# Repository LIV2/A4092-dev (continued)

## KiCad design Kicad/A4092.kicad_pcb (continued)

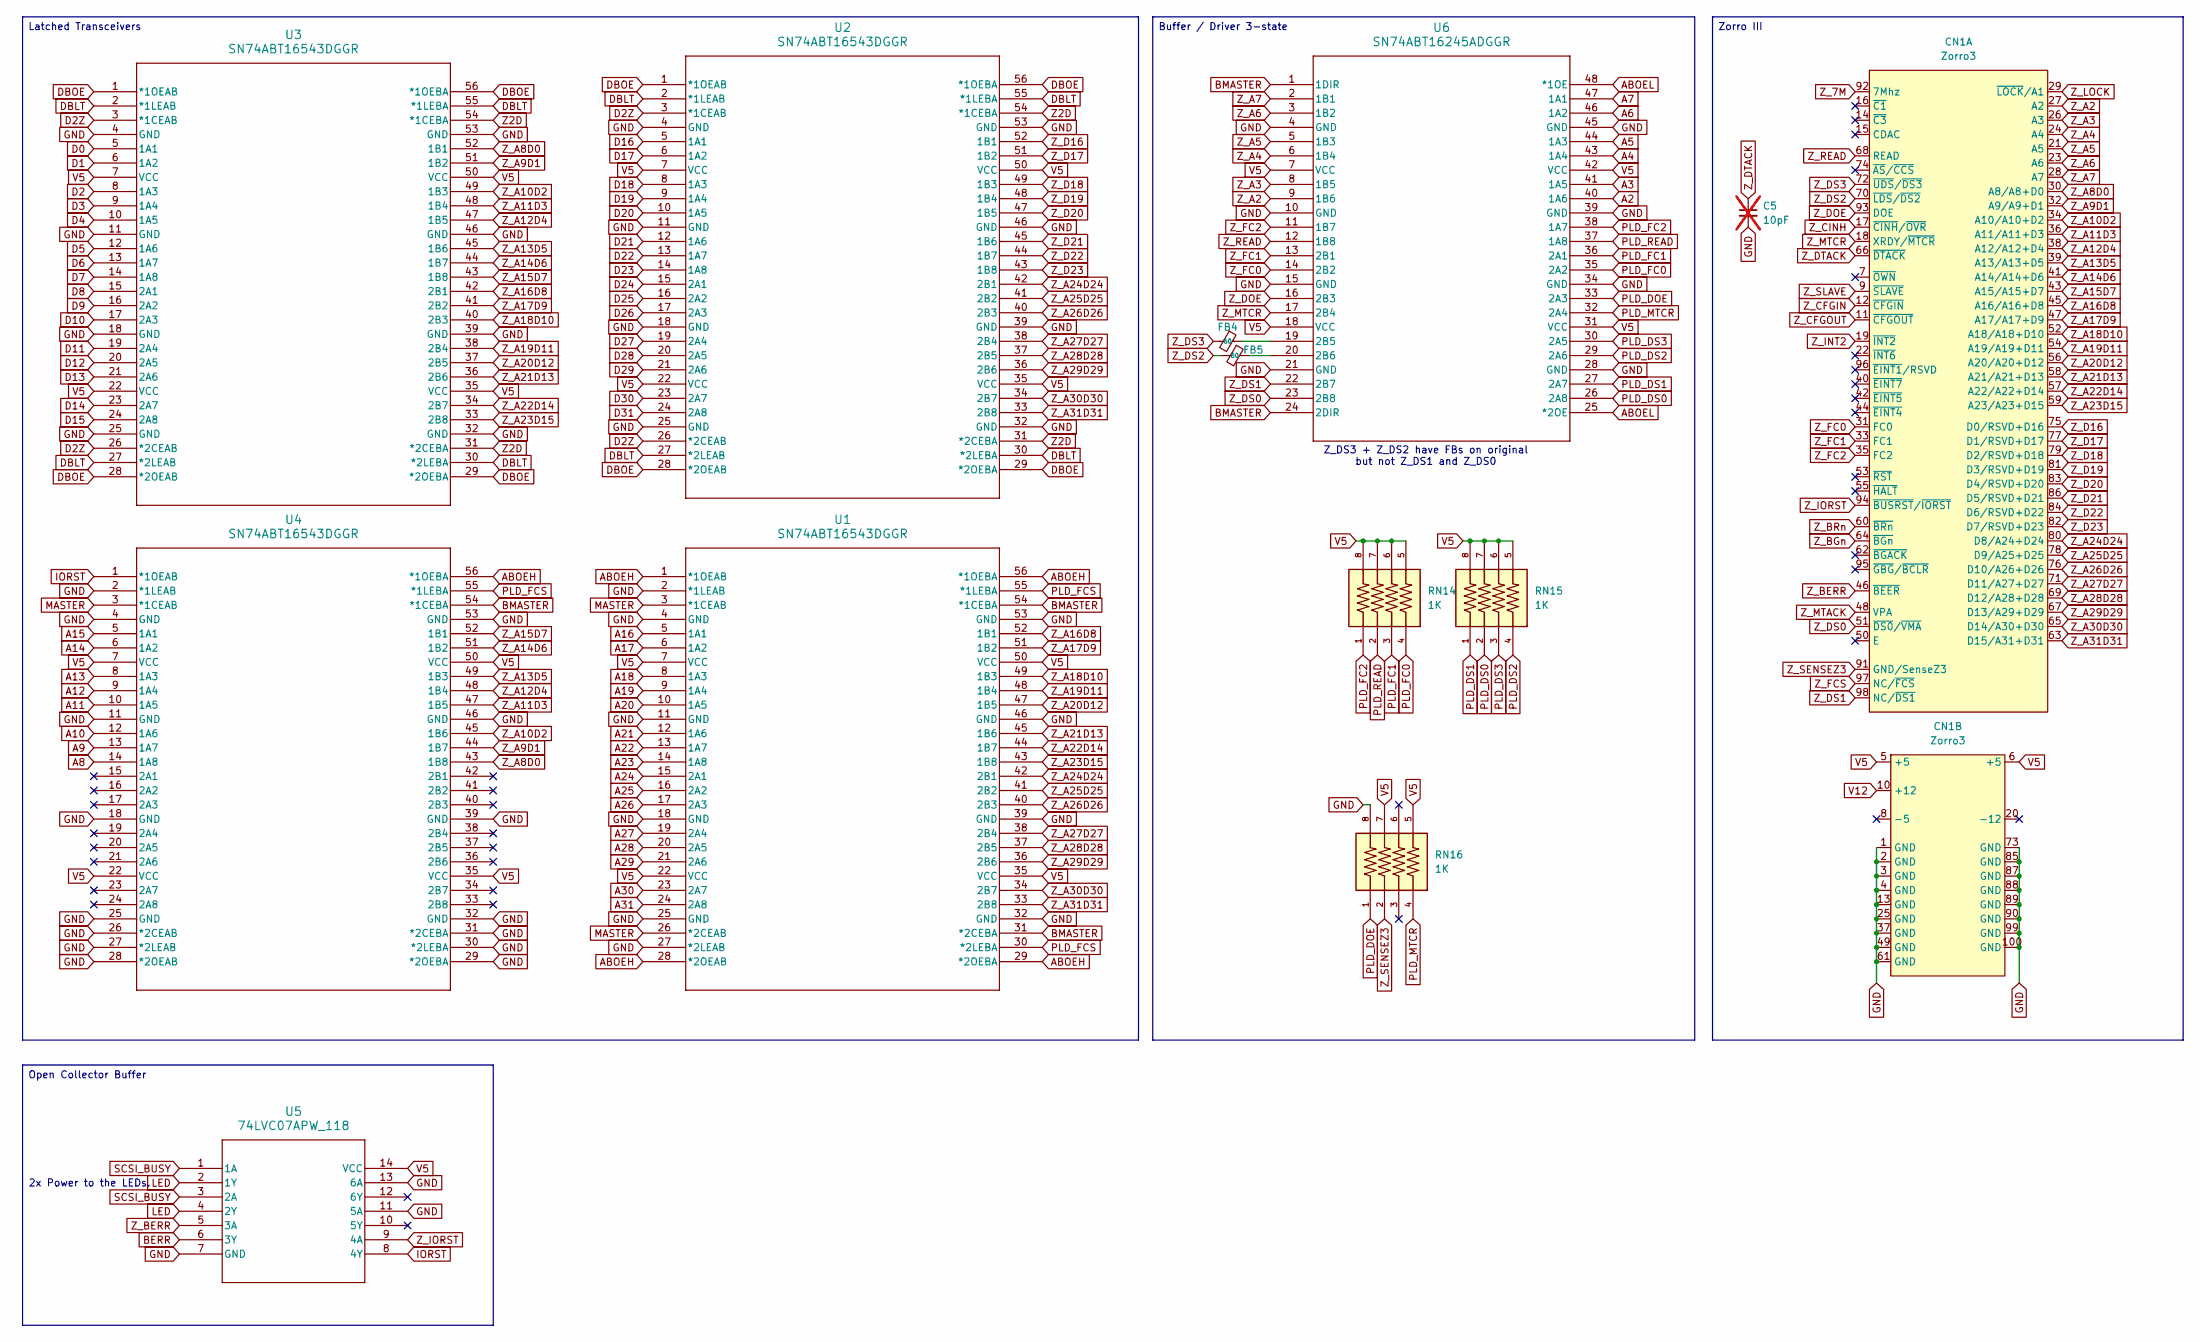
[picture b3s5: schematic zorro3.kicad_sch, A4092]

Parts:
C5: 10pF; C_0603_1608Metric_Pad1.08x0.95mm_HandSolder; not fitted
CN1: Zorro3; Zorro3-CardEdge
FB4, FB5: 60; C_0603_1608Metric_Pad1.08x0.95mm_HandSolder; LCSC Part # C95177
RN14, RN15, RN16: 1K; BO_CAY16; PARTREV V.9; LCSC Part # C784824
U1, U2, U3, U4: SN74ABT16543DGGR; DL56; LCSC Part # C2865087
U5: 74LVC07APW_118; TSSOP14_5P1X4P5_NEX; LCSC Part # C6051
U6: SN74ABT16245ADGGR; DGG48; LCSC Part # C130197

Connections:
A2: U6.40 (1A6); also elsewhere on the board
A3: U6.41 (1A5); also elsewhere on the board
A4: U6.43 (1A4); also elsewhere on the board
A5: U6.44 (1A3); also elsewhere on the board
A6: U6.46 (1A2); also elsewhere on the board
A7: U6.47 (1A1); also elsewhere on the board
A8: U4.14 (1A8); also elsewhere on the board
A9: U4.13 (1A7); also elsewhere on the board
A10: U4.12 (1A6); also elsewhere on the board
A11: U4.10 (1A5); also elsewhere on the board
A12: U4.9 (1A4); also elsewhere on the board
A13: U4.8 (1A3); also elsewhere on the board
A14: U4.6 (1A2); also elsewhere on the board
A15: U4.5 (1A1); also elsewhere on the board
A16: U1.5 (1A1); also elsewhere on the board
A17: U1.6 (1A2); also elsewhere on the board
A18: U1.8 (1A3); also elsewhere on the board
A19: U1.9 (1A4); also elsewhere on the board
A20: U1.10 (1A5); also elsewhere on the board
A21: U1.12 (1A6); also elsewhere on the board
A22: U1.13 (1A7); also elsewhere on the board
A23: U1.14 (1A8); also elsewhere on the board
A24: U1.15 (2A1); also elsewhere on the board
A25: U1.16 (2A2); also elsewhere on the board
A26: U1.17 (2A3); also elsewhere on the board
A27: U1.19 (2A4); also elsewhere on the board
A28: U1.20 (2A5); also elsewhere on the board
A29: U1.21 (2A6); also elsewhere on the board
A30: U1.23 (2A7); also elsewhere on the board
A31: U1.24 (2A8); also elsewhere on the board
ABOEH: U1.1 (*1OEAB), U1.28 (*2OEAB), U1.29 (*2OEBA), U1.56 (*1OEBA), U4.56 (*1OEBA); also elsewhere on the board
ABOEL: U6.25 (*2OE), U6.48 (*1OE); also elsewhere on the board
BERR: U5.6 (3Y); also elsewhere on the board
BMASTER: U1.31 (*2CEBA), U1.54 (*1CEBA), U4.54 (*1CEBA), U6.1 (1DIR), U6.24 (2DIR); also elsewhere on the board
D0: U3.5 (1A1); also elsewhere on the board
D1: U3.6 (1A2); also elsewhere on the board
D2: U3.8 (1A3); also elsewhere on the board
D2Z: U2.3 (*1CEAB), U2.26 (*2CEAB), U3.3 (*1CEAB), U3.26 (*2CEAB); also elsewhere on the board
D3: U3.9 (1A4); also elsewhere on the board
D4: U3.10 (1A5); also elsewhere on the board
D5: U3.12 (1A6); also elsewhere on the board
D6: U3.13 (1A7); also elsewhere on the board
D7: U3.14 (1A8); also elsewhere on the board
D8: U3.15 (2A1); also elsewhere on the board
D9: U3.16 (2A2); also elsewhere on the board
D10: U3.17 (2A3); also elsewhere on the board
D11: U3.19 (2A4); also elsewhere on the board
D12: U3.20 (2A5); also elsewhere on the board
D13: U3.21 (2A6); also elsewhere on the board
D14: U3.23 (2A7); also elsewhere on the board
D15: U3.24 (2A8); also elsewhere on the board
D16: U2.5 (1A1); also elsewhere on the board
D17: U2.6 (1A2); also elsewhere on the board
D18: U2.8 (1A3); also elsewhere on the board
D19: U2.9 (1A4); also elsewhere on the board
D20: U2.10 (1A5); also elsewhere on the board
D21: U2.12 (1A6); also elsewhere on the board
D22: U2.13 (1A7); also elsewhere on the board
D23: U2.14 (1A8); also elsewhere on the board
D24: U2.15 (2A1); also elsewhere on the board
D25: U2.16 (2A2); also elsewhere on the board
D26: U2.17 (2A3); also elsewhere on the board
D27: U2.19 (2A4); also elsewhere on the board
D28: U2.20 (2A5); also elsewhere on the board
D29: U2.21 (2A6); also elsewhere on the board
D30: U2.23 (2A7); also elsewhere on the board
D31: U2.24 (2A8); also elsewhere on the board
DBLT: U2.2 (*1LEAB), U2.27 (*2LEAB), U2.30 (*2LEBA), U2.55 (*1LEBA), U3.2 (*1LEAB), U3.27 (*2LEAB), U3.30 (*2LEBA), U3.55 (*1LEBA); also elsewhere on the board
DBOE: U2.1 (*1OEAB), U2.28 (*2OEAB), U2.29 (*2OEBA), U2.56 (*1OEBA), U3.1 (*1OEAB), U3.28 (*2OEAB), U3.29 (*2OEBA), U3.56 (*1OEBA); also elsewhere on the board
GND: C5.2, CN1.1 (GND), CN1.2 (GND), CN1.3 (GND), CN1.4 (GND), CN1.13 (GND), CN1.25 (GND), CN1.37 (GND), CN1.49 (GND), CN1.61 (GND), CN1.73 (GND), CN1.85 (GND), CN1.87 (GND), CN1.88 (GND), CN1.89 (GND), CN1.90 (GND), CN1.99 (GND), CN1.100 (GND), RN16.8, U1.2 (*1LEAB), U1.4 (GND), U1.11 (GND), U1.18 (GND), U1.25 (GND), U1.27 (*2LEAB), U1.32 (GND), U1.39 (GND), U1.46 (GND), U1.53 (GND), U2.4 (GND), U2.11 (GND), U2.18 (GND), U2.25 (GND), U2.32 (GND), U2.39 (GND), U2.46 (GND), U2.53 (GND), U3.4 (GND), U3.11 (GND), U3.18 (GND), U3.25 (GND), U3.32 (GND), U3.39 (GND), U3.46 (GND), U3.53 (GND), U4.2 (*1LEAB), U4.4 (GND), U4.11 (GND), U4.18 (GND), U4.25 (GND), U4.26 (*2CEAB), U4.27 (*2LEAB), U4.28 (*2OEAB), U4.29 (*2OEBA), U4.30 (*2LEBA), U4.31 (*2CEBA), U4.32 (GND), U4.39 (GND), U4.46 (GND), U4.53 (GND), U5.7 (GND), U5.11 (5A), U5.13 (6A), U6.4 (GND), U6.10 (GND), U6.15 (GND), U6.21 (GND), U6.28 (GND), U6.34 (GND), U6.39 (GND), U6.45 (GND); also elsewhere on the board
IORST: U4.1 (*1OEAB), U5.8 (4Y); also elsewhere on the board
LED: U5.2 (1Y), U5.4 (2Y); also elsewhere on the board
MASTER: U1.3 (*1CEAB), U1.26 (*2CEAB), U4.3 (*1CEAB); also elsewhere on the board
unnamed: FB4.1, U6.19 (2B5)
unnamed: FB5.1, U6.20 (2B6)
PLD_DOE: RN16.1, U6.33 (2A3); also elsewhere on the board
PLD_DS0: RN15.2, U6.26 (2A8); also elsewhere on the board
PLD_DS1: RN15.1, U6.27 (2A7); also elsewhere on the board
PLD_DS2: RN15.4, U6.29 (2A6); also elsewhere on the board
PLD_DS3: RN15.3, U6.30 (2A5); also elsewhere on the board
PLD_FC0: RN14.4, U6.35 (2A2); also elsewhere on the board
PLD_FC1: RN14.3, U6.36 (2A1); also elsewhere on the board
PLD_FC2: RN14.1, U6.38 (1A7); also elsewhere on the board
PLD_FCS: U1.30 (*2LEBA), U1.55 (*1LEBA), U4.55 (*1LEBA); also elsewhere on the board
PLD_MTCR: RN16.4, U6.32 (2A4); also elsewhere on the board
PLD_READ: RN14.2, U6.37 (1A8); also elsewhere on the board
SCSI_BUSY: U5.1 (1A), U5.3 (2A); also elsewhere on the board
V5: CN1.5 (+5), CN1.6 (+5), RN14.5, RN14.6, RN14.7, RN14.8, RN15.5, RN15.6, RN15.7, RN15.8, RN16.5, RN16.7, U1.7 (VCC), U1.22 (VCC), U1.35 (VCC), U1.50 (VCC), U2.7 (VCC), U2.22 (VCC), U2.35 (VCC), U2.50 (VCC), U3.7 (VCC), U3.22 (VCC), U3.35 (VCC), U3.50 (VCC), U4.7 (VCC), U4.22 (VCC), U4.35 (VCC), U4.50 (VCC), U5.14 (VCC), U6.7 (VCC), U6.18 (VCC), U6.31 (VCC), U6.42 (VCC); also elsewhere on the board
V12: CN1.10 (+12); also elsewhere on the board
Z2D: U2.31 (*2CEBA), U2.54 (*1CEBA), U3.31 (*2CEBA), U3.54 (*1CEBA); also elsewhere on the board
Z_7M: CN1.92 (7Mhz); also elsewhere on the board
Z_A2: CN1.27 (A2), U6.9 (1B6)
Z_A3: CN1.26 (A3), U6.8 (1B5)
Z_A4: CN1.24 (A4), U6.6 (1B4)
Z_A5: CN1.21 (A5), U6.5 (1B3)
Z_A6: CN1.23 (A6), U6.3 (1B2)
Z_A7: CN1.28 (A7), U6.2 (1B1)
Z_A8D0: CN1.30 (A8/A8+D0), U3.52 (1B1), U4.43 (1B8)
Z_A9D1: CN1.32 (A9/A9+D1), U3.51 (1B2), U4.44 (1B7)
Z_A10D2: CN1.34 (A10/A10+D2), U3.49 (1B3), U4.45 (1B6)
Z_A11D3: CN1.36 (A11/A11+D3), U3.48 (1B4), U4.47 (1B5)
Z_A12D4: CN1.38 (A12/A12+D4), U3.47 (1B5), U4.48 (1B4)
Z_A13D5: CN1.39 (A13/A13+D5), U3.45 (1B6), U4.49 (1B3)
Z_A14D6: CN1.41 (A14/A14+D6), U3.44 (1B7), U4.51 (1B2)
Z_A15D7: CN1.43 (A15/A15+D7), U3.43 (1B8), U4.52 (1B1)
Z_A16D8: CN1.45 (A16/A16+D8), U1.52 (1B1), U3.42 (2B1)
Z_A17D9: CN1.47 (A17/A17+D9), U1.51 (1B2), U3.41 (2B2)
Z_A18D10: CN1.52 (A18/A18+D10), U1.49 (1B3), U3.40 (2B3)
Z_A19D11: CN1.54 (A19/A19+D11), U1.48 (1B4), U3.38 (2B4)
Z_A20D12: CN1.56 (A20/A20+D12), U1.47 (1B5), U3.37 (2B5)
Z_A21D13: CN1.58 (A21/A21+D13), U1.45 (1B6), U3.36 (2B6)
Z_A22D14: CN1.57 (A22/A22+D14), U1.44 (1B7), U3.34 (2B7)
Z_A23D15: CN1.59 (A23/A23+D15), U1.43 (1B8), U3.33 (2B8)
Z_A24D24: CN1.80 (D8/A24+D24), U1.42 (2B1), U2.42 (2B1)
Z_A25D25: CN1.78 (D9/A25+D25), U1.41 (2B2), U2.41 (2B2)
Z_A26D26: CN1.76 (D10/A26+D26), U1.40 (2B3), U2.40 (2B3)
Z_A27D27: CN1.71 (D11/A27+D27), U1.38 (2B4), U2.38 (2B4)
Z_A28D28: CN1.69 (D12/A28+D28), U1.37 (2B5), U2.37 (2B5)
Z_A29D29: CN1.67 (D13/A29+D29), U1.36 (2B6), U2.36 (2B6)
Z_A30D30: CN1.65 (D14/A30+D30), U1.34 (2B7), U2.34 (2B7)
Z_A31D31: CN1.63 (D15/A31+D31), U1.33 (2B8), U2.33 (2B8)
Z_BERR: CN1.46 (~BEER), U5.5 (3A)
Z_BGn: CN1.64 (~BGn); also elsewhere on the board
Z_BRn: CN1.60 (~BRn); also elsewhere on the board
Z_CFGIN: CN1.12 (~CFGIN); also elsewhere on the board
Z_CFGOUT: CN1.11 (~CFGOUT); also elsewhere on the board
Z_CINH: CN1.17 (~CINH/~OVR); also elsewhere on the board
Z_D16: CN1.75 (D0/RSVD+D16), U2.52 (1B1)
Z_D17: CN1.77 (D1/RSVD+D17), U2.51 (1B2)
Z_D18: CN1.79 (D2/RSVD+D18), U2.49 (1B3)
Z_D19: CN1.81 (D3/RSVD+D19), U2.48 (1B4)
Z_D20: CN1.83 (D4/RSVD+D20), U2.47 (1B5)
Z_D21: CN1.86 (D5/RSVD+D21), U2.45 (1B6)
Z_D22: CN1.84 (D6/RSVD+D22), U2.44 (1B7)
Z_D23: CN1.82 (D7/RSVD+D23), U2.43 (1B8)
Z_DOE: CN1.93 (DOE), U6.16 (2B3)
Z_DS0: CN1.51 (~DS0/~VMA), U6.23 (2B8)
Z_DS1: CN1.98 (NC/~DS1), U6.22 (2B7)
Z_DS2: CN1.70 (~LDS/~DS2), FB5.2
Z_DS3: CN1.72 (~UDS/~DS3), FB4.2
Z_DTACK: C5.1, CN1.66 (~DTACK); also elsewhere on the board
Z_FC0: CN1.31 (FC0), U6.14 (2B2)
Z_FC1: CN1.33 (FC1), U6.13 (2B1)
Z_FC2: CN1.35 (FC2), U6.11 (1B7)
Z_FCS: CN1.97 (NC/~FCS); also elsewhere on the board
Z_INT2: CN1.19 (~INT2); also elsewhere on the board
Z_IORST: CN1.94 (~BUSRST/~IORST), U5.9 (4A)
Z_LOCK: CN1.29 (~LOCK/A1); also elsewhere on the board
Z_MTACK: CN1.48 (VPA); also elsewhere on the board
Z_MTCR: CN1.18 (XRDY/~MTCR), U6.17 (2B4)
Z_READ: CN1.68 (READ), U6.12 (1B8)
Z_SENSEZ3: CN1.91 (GND/SenseZ3), RN16.2; also elsewhere on the board
Z_SLAVE: CN1.9 (~SLAVE); also elsewhere on the board

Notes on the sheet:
Z_DS3 + Z_DS2 have FBs on original but not Z_DS1 and Z_DS0
2x Power to the LEDs.
Buffer / Driver 3-state
Latched Transceivers
Open Collector Buffer
Zorro III

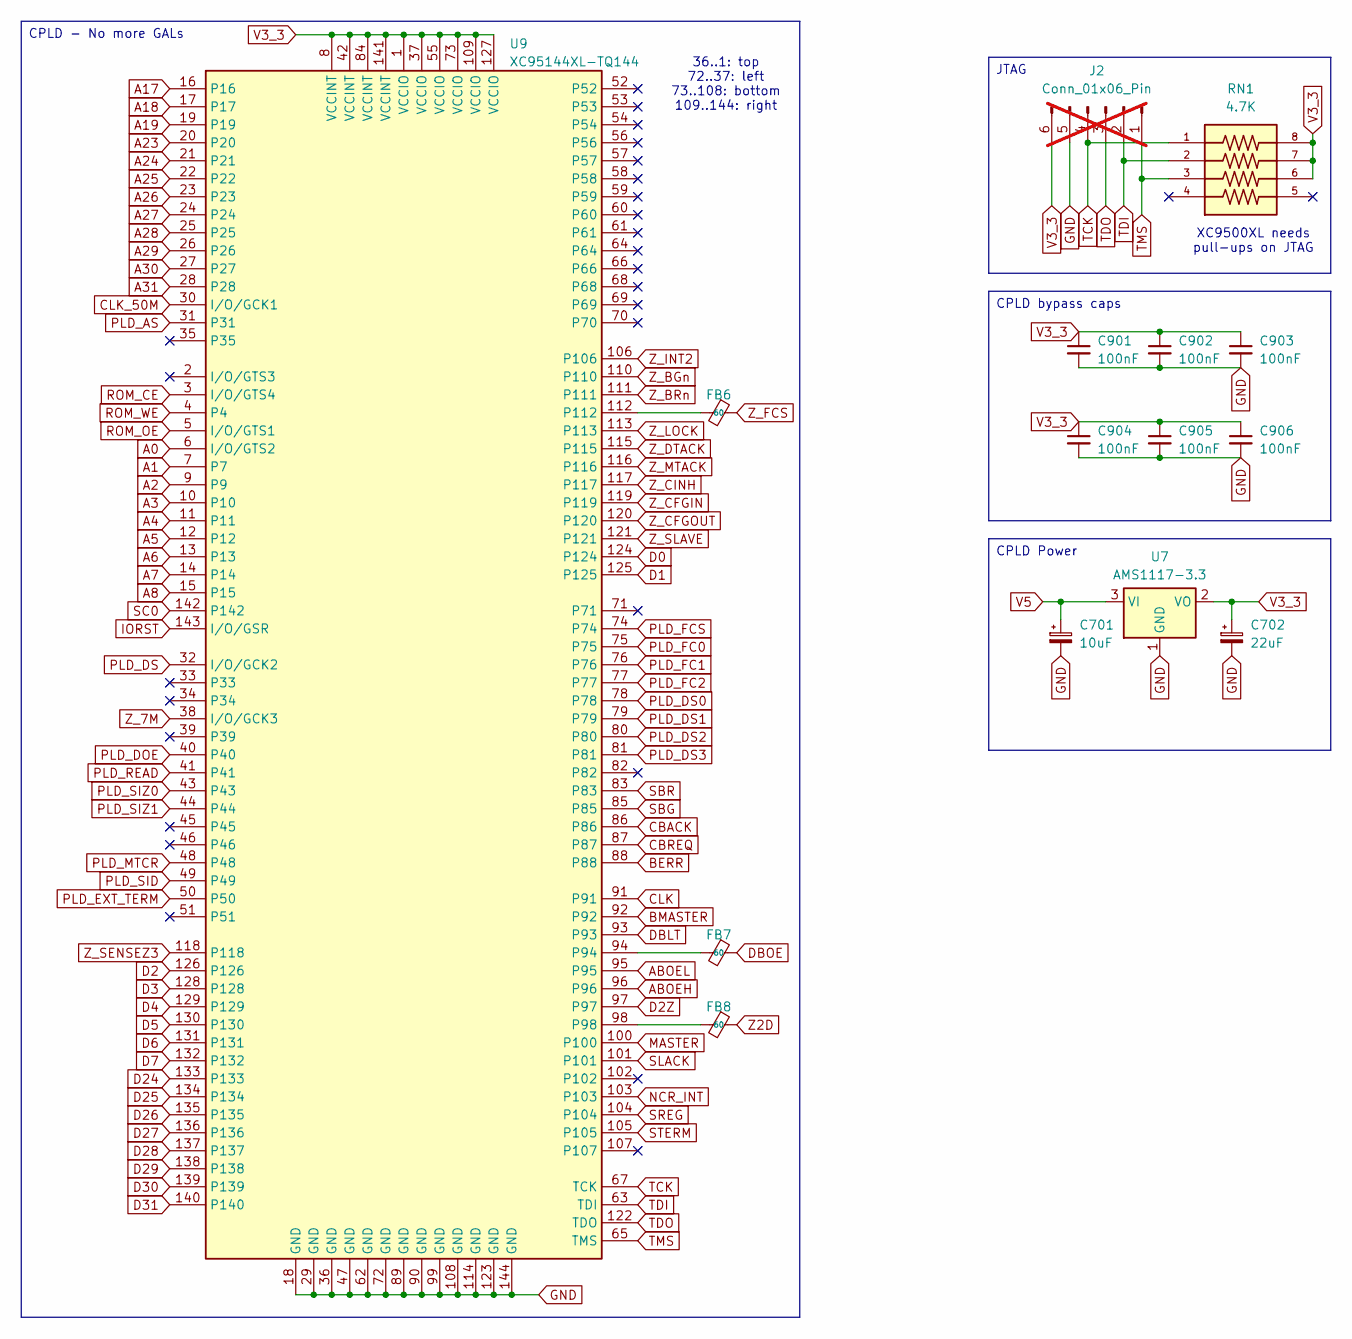
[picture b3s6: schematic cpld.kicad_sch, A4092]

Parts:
C701: 10uF; CP_EIA-3528-15_AVX-H_HandSolder; LCSC Part # C7194
C702: 22uF; CP_EIA-3528-15_AVX-H_HandSolder; LCSC Part # C696813
C901, C902, C903, C904, C905, C906: 100nF; C_0603_1608Metric_Pad1.08x0.95mm_HandSolder; LCSC Part # C14663
FB6, FB7, FB8: 60; C_0603_1608Metric_Pad1.08x0.95mm_HandSolder; LCSC Part # C95177
J2: Conn_01x06_Pin; PinHeader_1x06_P2.54mm_Vertical; LCSC Part # C6332199; not fitted
RN1: 4.7K; BO_CAY16; PARTREV V.9; LCSC Part # C327044
U7: AMS1117-3.3; SOT-223-3_TabPin2; LCSC Part # C6186
U9: XC95144XL-TQ144; 144-TQFP_XIL; LCSC Part # C1521137

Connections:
A0: U9.6 (I/O/GTS2); also elsewhere on the board
A1: U9.7; also elsewhere on the board
A2: U9.9; also elsewhere on the board
A3: U9.10; also elsewhere on the board
A4: U9.11; also elsewhere on the board
A5: U9.12; also elsewhere on the board
A6: U9.13; also elsewhere on the board
A7: U9.14; also elsewhere on the board
A8: U9.15; also elsewhere on the board
A17: U9.16; also elsewhere on the board
A18: U9.17; also elsewhere on the board
A19: U9.19; also elsewhere on the board
A23: U9.20; also elsewhere on the board
A24: U9.21; also elsewhere on the board
A25: U9.22; also elsewhere on the board
A26: U9.23; also elsewhere on the board
A27: U9.24; also elsewhere on the board
A28: U9.25; also elsewhere on the board
A29: U9.26; also elsewhere on the board
A30: U9.27; also elsewhere on the board
A31: U9.28; also elsewhere on the board
ABOEH: U9.96; also elsewhere on the board
ABOEL: U9.95; also elsewhere on the board
BERR: U9.88; also elsewhere on the board
BMASTER: U9.92; also elsewhere on the board
CBACK: U9.86; also elsewhere on the board
CBREQ: U9.87; also elsewhere on the board
CLK: U9.91; also elsewhere on the board
CLK_50M: U9.30 (I/O/GCK1); also elsewhere on the board
D0: U9.124; also elsewhere on the board
D1: U9.125; also elsewhere on the board
D2: U9.126; also elsewhere on the board
D2Z: U9.97; also elsewhere on the board
D3: U9.128; also elsewhere on the board
D4: U9.129; also elsewhere on the board
D5: U9.130; also elsewhere on the board
D6: U9.131; also elsewhere on the board
D7: U9.132; also elsewhere on the board
D24: U9.133; also elsewhere on the board
D25: U9.134; also elsewhere on the board
D26: U9.135; also elsewhere on the board
D27: U9.136; also elsewhere on the board
D28: U9.137; also elsewhere on the board
D29: U9.138; also elsewhere on the board
D30: U9.139; also elsewhere on the board
D31: U9.140; also elsewhere on the board
DBLT: U9.93; also elsewhere on the board
DBOE: FB7.1; also elsewhere on the board
GND: C701.2, C702.2, C901.2, C902.2, C903.2, C904.2, C905.2, C906.2, J2.5, U7.1 (GND), U9.18 (GND), U9.29 (GND), U9.36 (GND), U9.47 (GND), U9.62 (GND), U9.72 (GND), U9.89 (GND), U9.90 (GND), U9.99 (GND), U9.108 (GND), U9.114 (GND), U9.123 (GND), U9.144 (GND); also elsewhere on the board
IORST: U9.143 (I/O/GSR); also elsewhere on the board
MASTER: U9.100; also elsewhere on the board
NCR_INT: U9.103; also elsewhere on the board
unnamed: FB7.2, U9.94
unnamed: FB8.2, U9.98
unnamed: FB6.2, U9.112
PLD_AS: U9.31; also elsewhere on the board
PLD_DOE: U9.40; also elsewhere on the board
PLD_DS: U9.32 (I/O/GCK2); also elsewhere on the board
PLD_DS0: U9.78; also elsewhere on the board
PLD_DS1: U9.79; also elsewhere on the board
PLD_DS2: U9.80; also elsewhere on the board
PLD_DS3: U9.81; also elsewhere on the board
PLD_EXT_TERM: U9.50; also elsewhere on the board
PLD_FC0: U9.75; also elsewhere on the board
PLD_FC1: U9.76; also elsewhere on the board
PLD_FC2: U9.77; also elsewhere on the board
PLD_FCS: U9.74; also elsewhere on the board
PLD_MTCR: U9.48; also elsewhere on the board
PLD_READ: U9.41; also elsewhere on the board
PLD_SID: U9.49; also elsewhere on the board
PLD_SIZ0: U9.43; also elsewhere on the board
PLD_SIZ1: U9.44; also elsewhere on the board
ROM_CE: U9.3 (I/O/GTS4); also elsewhere on the board
ROM_OE: U9.5 (I/O/GTS1); also elsewhere on the board
ROM_WE: U9.4; also elsewhere on the board
SBG: U9.85; also elsewhere on the board
SBR: U9.83; also elsewhere on the board
SC0: U9.142; also elsewhere on the board
SLACK: U9.101; also elsewhere on the board
SREG: U9.104; also elsewhere on the board
STERM: U9.105; also elsewhere on the board
TCK: J2.4, RN1.1, U9.67 (TCK)
TDI: J2.2, RN1.2, U9.63 (TDI)
TDO: J2.3, U9.122 (TDO)
TMS: J2.1, RN1.3, U9.65 (TMS)
V3_3: C702.1, C901.1, C902.1, C903.1, C904.1, C905.1, C906.1, J2.6, RN1.6, RN1.7, RN1.8, U7.2 (VO), U9.1 (VCCIO), U9.8 (VCCINT), U9.37 (VCCIO), U9.42 (VCCINT), U9.55 (VCCIO), U9.73 (VCCIO), U9.84 (VCCINT), U9.109 (VCCIO), U9.127 (VCCIO), U9.141 (VCCINT)
V5: C701.1, U7.3 (VI); also elsewhere on the board
Z2D: FB8.1; also elsewhere on the board
Z_7M: U9.38 (I/O/GCK3); also elsewhere on the board
Z_BGn: U9.110; also elsewhere on the board
Z_BRn: U9.111; also elsewhere on the board
Z_CFGIN: U9.119; also elsewhere on the board
Z_CFGOUT: U9.120; also elsewhere on the board
Z_CINH: U9.117; also elsewhere on the board
Z_DTACK: U9.115; also elsewhere on the board
Z_FCS: FB6.1; also elsewhere on the board
Z_INT2: U9.106; also elsewhere on the board
Z_LOCK: U9.113; also elsewhere on the board
Z_MTACK: U9.116; also elsewhere on the board
Z_SENSEZ3: U9.118; also elsewhere on the board
Z_SLAVE: U9.121; also elsewhere on the board

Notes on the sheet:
36..1: top 72..37: left 73..108: bottom 109..144: right
XC9500XL needs pull-ups on JTAG
CPLD - No more GALs
JTAG
CPLD Power
CPLD bypass caps

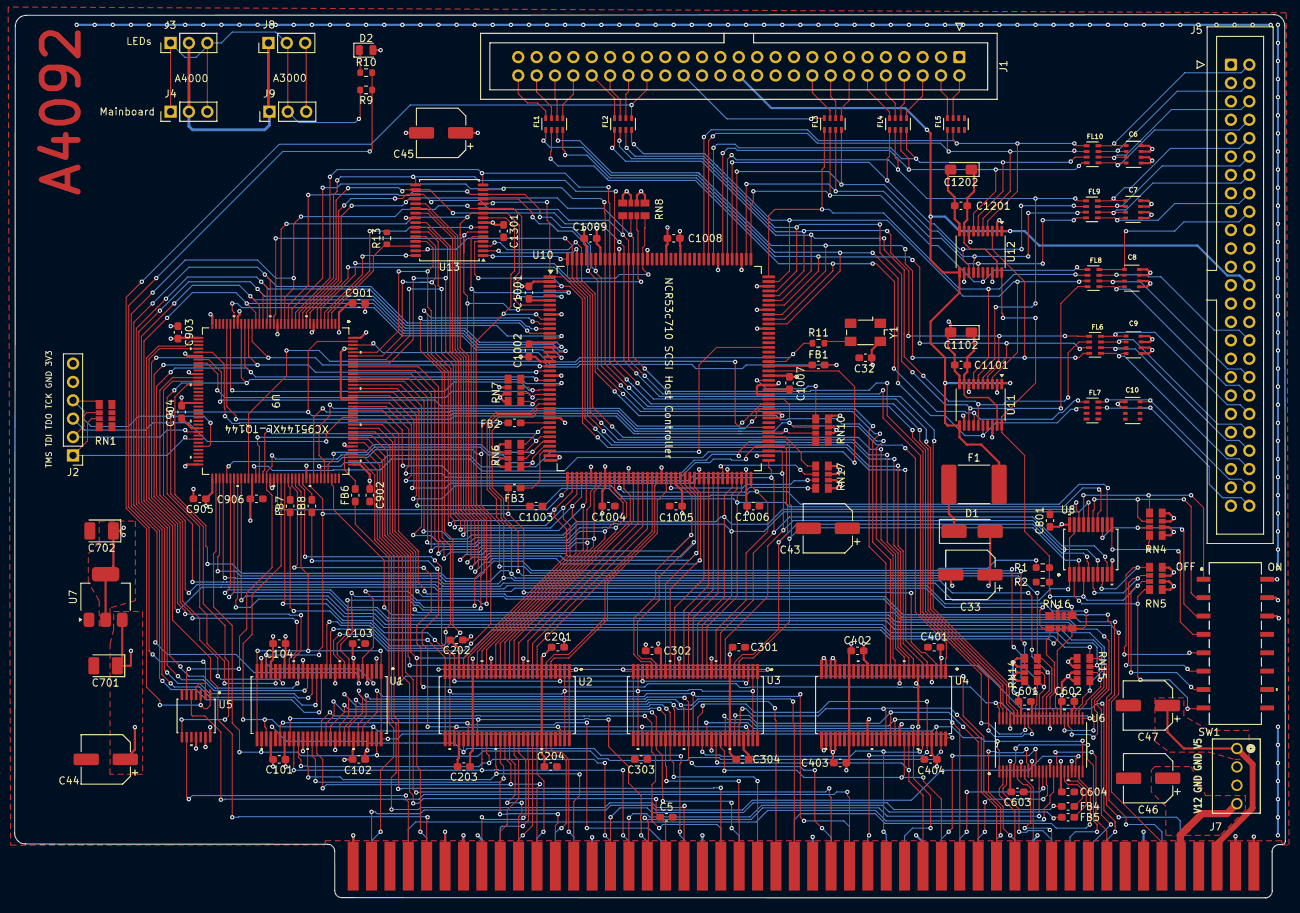
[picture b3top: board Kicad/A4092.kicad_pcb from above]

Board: 4 copper layers, 175.6 x 122.1 mm, 118 parts (0 on the bottom side), 260 nets.

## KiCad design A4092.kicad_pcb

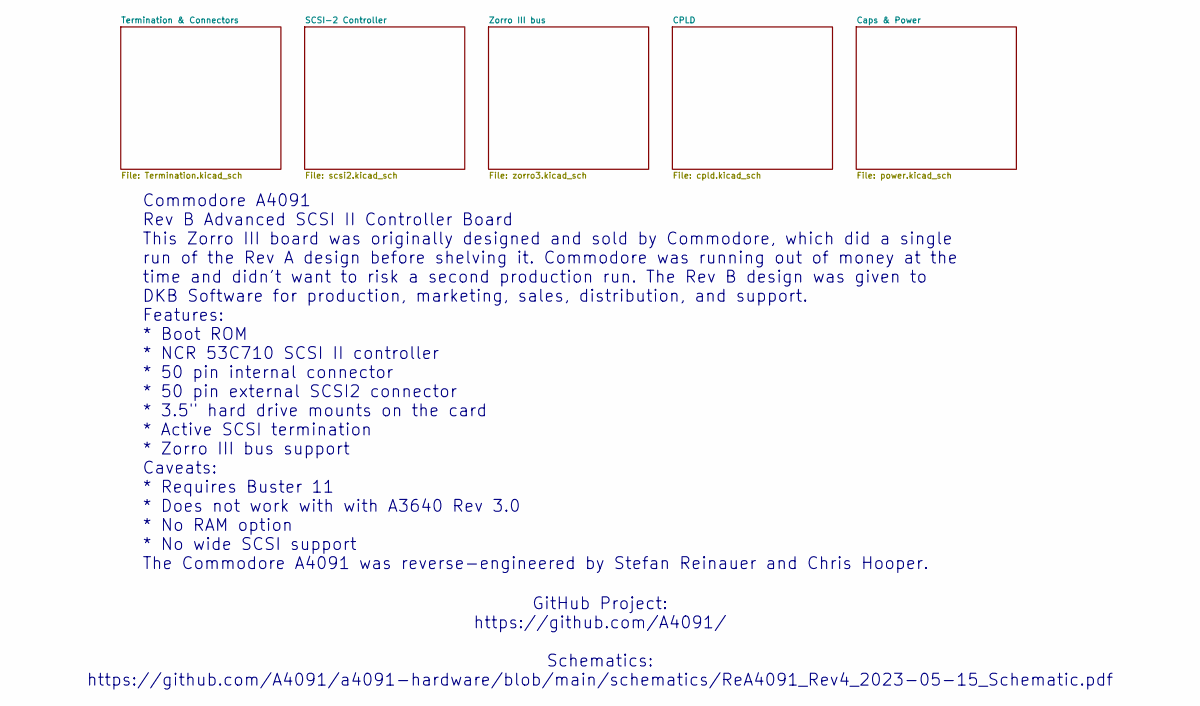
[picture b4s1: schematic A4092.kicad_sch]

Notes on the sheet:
Commodore A4091 Rev B Advanced SCSI II Controller Board This Zorro III board was originally designed and sold by Commodore, which did a single run of the Rev A design before shelving it. Commodore was running out of money at the time and didn't want to risk a second production run. The Rev B design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
GitHub Project: https://github.com/A4091/ Schematics: https://github.com/A4091/a4091-hardware/blob/main/schematics/ReA4091_Rev4_2023-05-15_Schematic.pdf

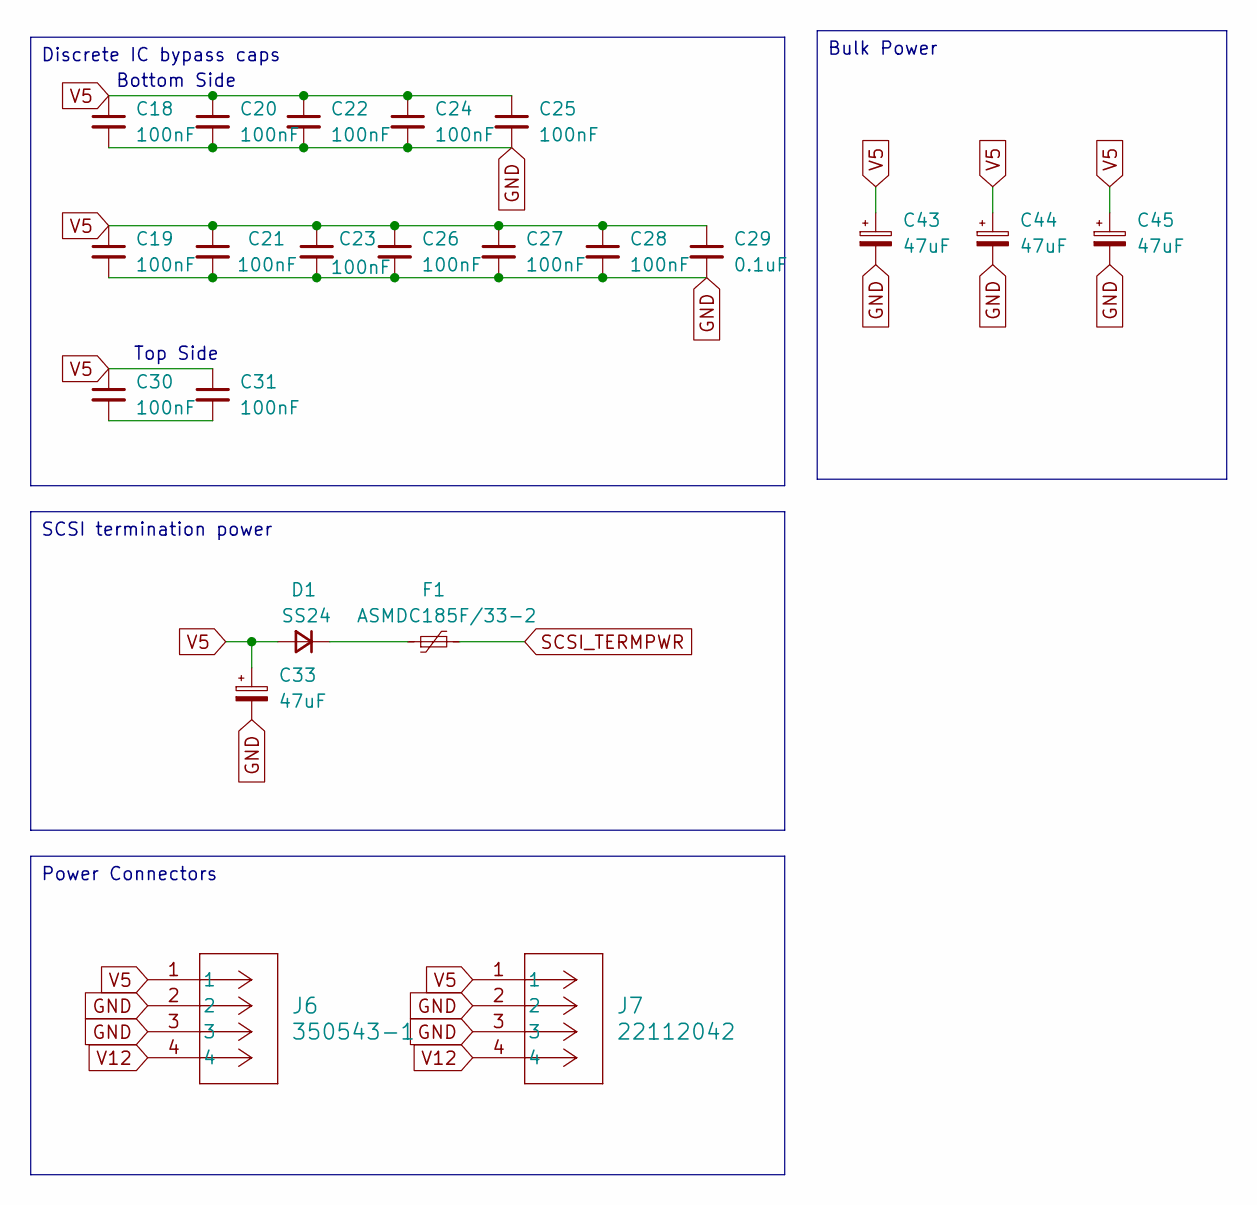
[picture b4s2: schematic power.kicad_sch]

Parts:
C18, C19, C20, C21, C22, C23, C24, C25, C26, C27, C28, C30, C31: 100nF; C_0603_1608Metric_Pad1.08x0.95mm_HandSolder
C29: 0.1uF; C_0603_1608Metric_Pad1.08x0.95mm_HandSolder
C33, C43, C44, C45: 47uF; CP_Elec_6.3x7.7
D1: SS24; D_SMA_Handsoldering
F1: ASMDC185F/33-2; Fuse_2920_7451Metric_Pad2.10x5.45mm_HandSolder
J6: 350543-1; CONN_350543-1_TYC
J7: 22112042; CONN_A-6373-04A_MOL

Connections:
unnamed: C30.2, C31.2
unnamed: D1.1 (K), F1.1
SCSI_TERMPWR: F1.2; also elsewhere on the board
V5: C18.1, C19.1, C20.1, C21.1, C22.1, C23.1, C24.1, C25.1, C26.1, C27.1, C28.1, C29.1, C30.1, C31.1, C33.1, C43.1, C44.1, C45.1, D1.2 (A), J6.1, J7.1; also elsewhere on the board
V12: J6.4, J7.4; also elsewhere on the board

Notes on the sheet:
Bottom Side
Top Side
SCSI termination power
Power Connectors
Discrete IC bypass caps
Bulk Power
